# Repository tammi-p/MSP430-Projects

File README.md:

# MSP430-Projects
This repository contains the codes for and descriptions of my embedded systems projects using the MSP430 microcontroller.

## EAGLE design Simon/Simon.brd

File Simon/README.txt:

Simon Game

Description:
The Simon Game is a device that plays a series of tones and lights, which the player needs to repeat. This sequence becomes longer and longer for each turn that the player correctly repeats it.

Components: 4 buttons with corresponding LEDs and tones

How it works: 
1. The device, called "Simon," will play a tone and light up an LED corresponding to pressing a random button
2. Player must repeat the sequence Simon played by pushing the correct button
3. If player succeeds, the sequence becomes longer by 1 tone/light, player must repeat the new sequence, and so on
4. A maximum sequence length is set in the code
  a. If player succeeds to last round -> WIN
  b. If player presses wrong button or waits too long to press a button (timeout) -> LOSE
  * WIN and LOSE are distinguished by unique tones and light sequences
  
Main parts of the code:
  State 0 - LOSE sequence is played until any button is pressed
  State 1 - Simon's turn and player's turn
  State 2 - WIN sequence is played until any button is pressed
  
  State 0
    1. A random button sequence is generated
    2. LOSE sequence is played until any button is pressed -> State 1
  State 1
    * A variable called turn, initialized to 1, keeps track of the turn number
    1. Simon plays (length of sequence played depends on the value of the variable turn)
    2. If timed out or player pressed wrong button -> State = 0
    3. If player plays entire sequence correctly -> State = 2
    4. Else, (player played correct sequence but we are not at the final turn yet) -> turn is incremented by 1 and State 1 is repeated
  State 2
    1. Play WIN sequence
    2. If a button is pressed, generate a random sequence and State = 1.
 * Pressing a button enters an ISR, which contains code checking if button pressed is correct

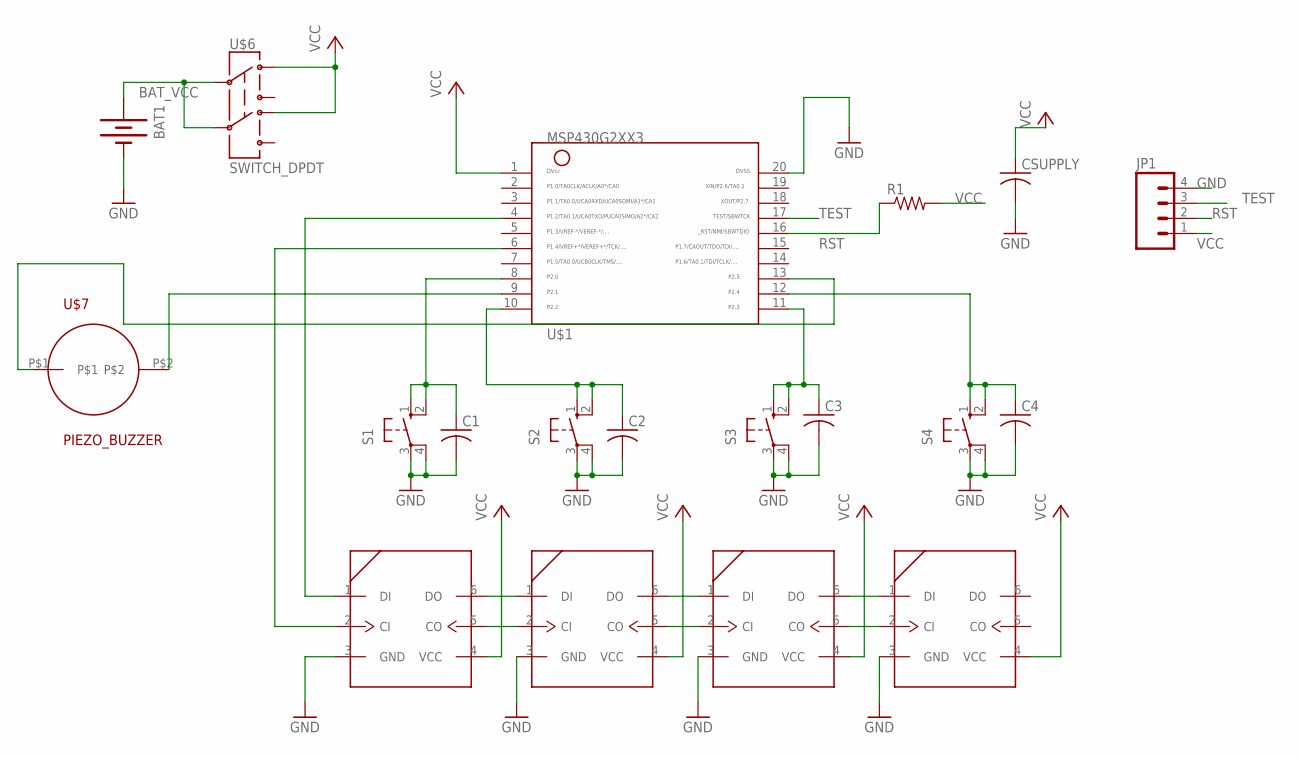
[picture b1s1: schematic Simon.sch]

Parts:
BAT1: BATTERY; BATTERY_PACK_2AA
C1, C2, C3, C4: C-USC1206; C1206
CSUPPLY: C-USC1206; C1206
JP1: M04LOCK; 1X04_LOCK
LED1, LED2, LED3, LED4: APA102; 5050
R1: R-US_R1206; R1206
S1, S2, S3, S4: 10-XX; B3F-10XX
U$1: MSP430G2XX3TSSOP; PW20
U$6: SWITCH_DPDT; JS_DPDT_TH
U$7: PIEZO_BUZZER

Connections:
BAT_VCC: BAT1.3V (+), U$6.2, U$6.5
GND: BAT1.GND (-), C1.2, C2.2, C3.2, C4.2, CSUPPLY.2, JP1.4, LED1.3 (GND), LED2.3 (GND), LED3.3 (GND), LED4.3 (GND), S1.3, S1.4 (P1), S2.3, S2.4 (P1), S3.3, S3.4 (P1), S4.3, S4.4 (P1), U$1.20
unnamed: LED1.6 (DO), LED2.1 (DI)
unnamed: LED1.5 (CO), LED2.2 (CI)
unnamed: LED2.6 (DO), LED3.1 (DI)
unnamed: LED2.5 (CO), LED3.2 (CI)
unnamed: LED3.6 (DO), LED4.1 (DI)
unnamed: LED3.5 (CO), LED4.2 (CI)
unnamed: LED1.1 (DI), U$1.4
unnamed: LED1.2 (CI), U$1.6
unnamed: U$1.9, U$7.P$2
unnamed: U$1.13, U$7.P$1
unnamed: C1.1, S1.1 (S), S1.2 (S1), U$1.8
unnamed: C2.1, S2.1 (S), S2.2 (S1), U$1.10
unnamed: C3.1, S3.1 (S), S3.2 (S1), U$1.11
unnamed: C4.1, S4.1 (S), S4.2 (S1), U$1.12
RST: JP1.2, R1.1, U$1.16
TEST: JP1.3, U$1.17
VCC: CSUPPLY.1, JP1.1, LED1.4 (VCC), LED2.4 (VCC), LED3.4 (VCC), LED4.4 (VCC), R1.2, U$1.1, U$6.1, U$6.4

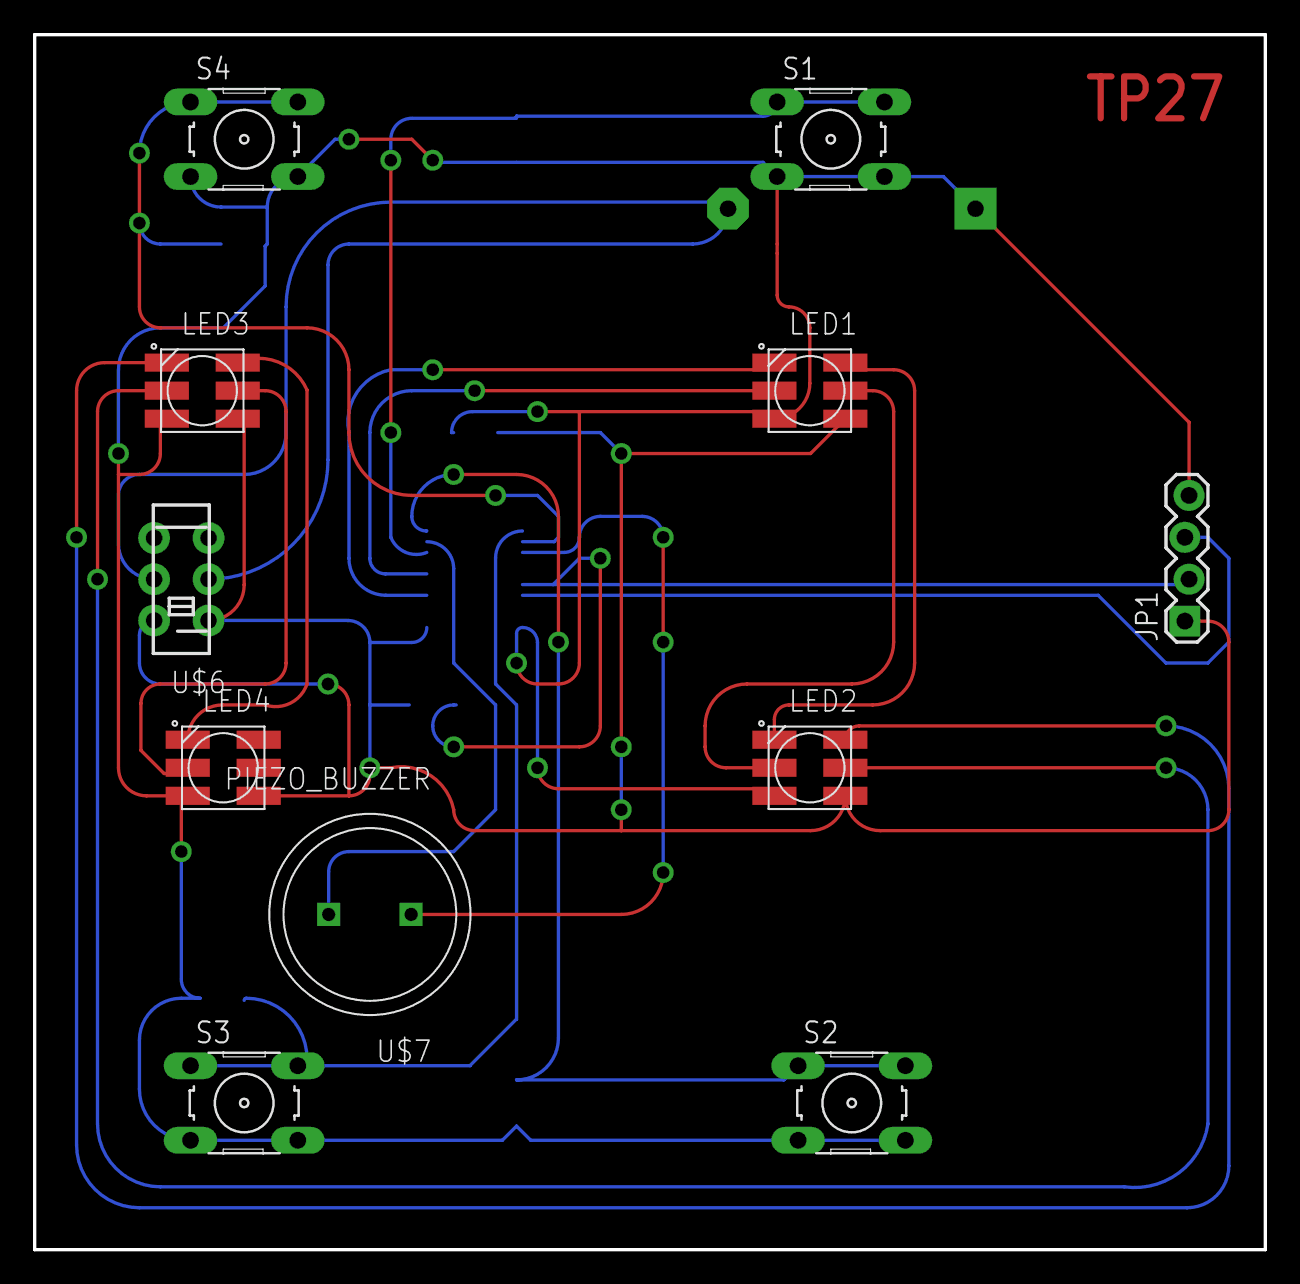
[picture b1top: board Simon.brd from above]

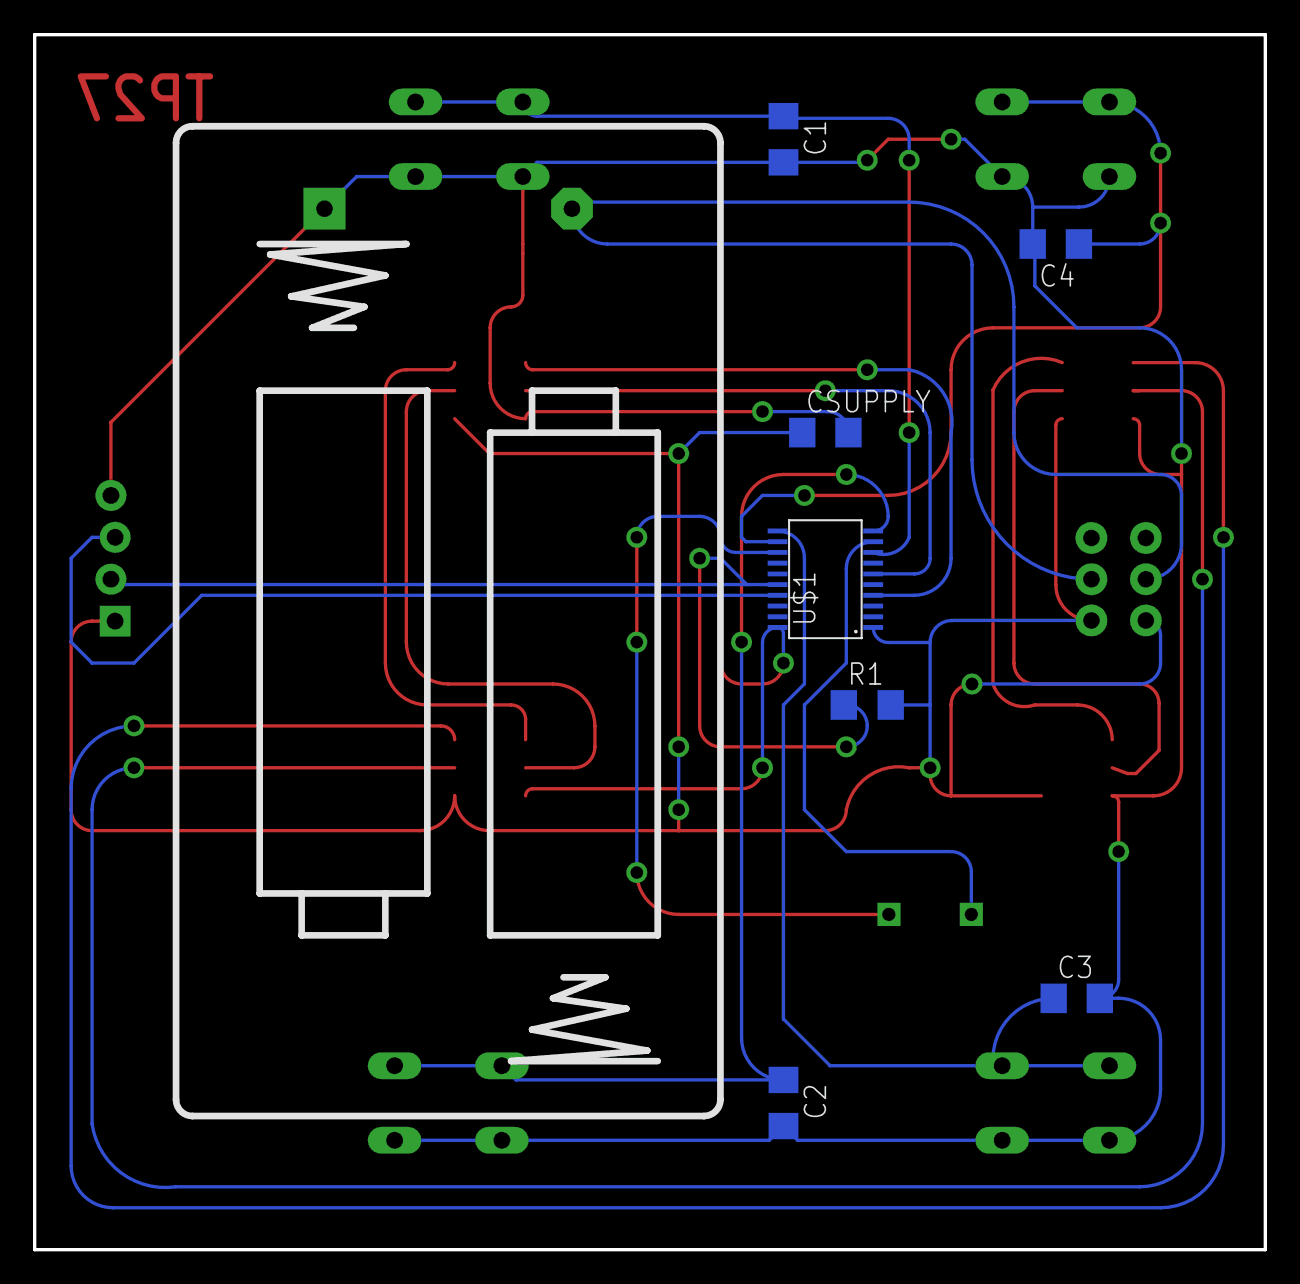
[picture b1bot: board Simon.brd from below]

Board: 2 copper layers, 74.6 x 73.7 mm, 19 parts (8 on the bottom side), 19 nets.

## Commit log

2019-12-23 Rename README.txt to README.md

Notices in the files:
parts and their libraries:
SparkFun: Licensing: CC v3.0 Share-Alike You are welcome to use this library for commercial purposes.
